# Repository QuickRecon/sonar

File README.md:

# Sonar

SonarMK2 is a standalone underwater sonar imaging system. An ESP32 drives a Blue Robotics Ping360 mechanical scanning sonar over RS-485, reads depth from a pressure sensor, and hosts a WiFi access point that serves a real-time polar sonar display to any browser that connects. The ESP hosts a webserver and "realtime" data is streamed over websockets, the page also uses the browser datastore to record the sonar information which can be downloaded and replayed using [text](Firmware/tools/replay.html). There is eventual intention to use the sonar for SLAM and some data analysis has occured in that direction, however this is ongoing.

## Hardware

The core is an ESP32-WROOM-32 with 2 MB flash and no PSRAM. The Ping360 communicates at 115200 baud over a half-duplex RS-485 link with automatic direction control on the DE pin. Depth comes from an MS5837-30BA pressure sensor on I2C at 400 kHz. Four status LEDs give a visual indicator of where the device is in its startup sequence.

Power input is from a battery connector (7–12 V) or USB-C, with an auto-select mux (TPS2121) handling the switch. A boost converter generates the 12 V rail for the sonar; a separate 5 V rail powers the RS-485 and external connectors. Both rails are software-controlled, so the firmware brings them up in sequence and checks power-good signals before proceeding.

The PCB also includes a CAN bus transceiver (TCAN334), the intended use is to allow for expansion to either DPV control/monitoring, or to be attached to a DiveCAN system so that rebreather information can be shown on the same display.

The hardware design files are in `EDA/` (KiCad schematic and PCB) and `CAD/` (FreeCAD housing assembly with STEP exports).

## Firmware

The firmware is built on ESP-IDF v6.0.0 and organized into nine components with no upward dependencies:

- **rs485** — UART1 half-duplex driver with automatic DE control
- **ping_protocol** — Binary frame encoder and decoder, pure C with no ESP-IDF coupling
- **ping360** — Scan task, configuration management, device probing
- **ms5837** — I2C pressure and depth sensor with full second-order compensation
- **led** — Four status LEDs indicating boot progress
- **power** — Rail enable/disable and battery voltage ADC
- **canbus** — CAN bus init and send (scaffolded, not called from main, will eventually have DiveCAN layer)
- **wifi_ap** — WiFi access point with captive portal DNS
- **web_server** — HTTPS file serving and WebSocket broadcast

### TLS Certificates

The web server uses HTTPS with a self-signed certificate. Generate the cert and key before building:

```bash
mkdir -p Firmware/certs
openssl req -x509 -newkey ec -pkeyopt ec_paramgen_curve:prime256v1 \
  -keyout Firmware/certs/server.key -out Firmware/certs/server.pem \
  -days 3650 -nodes -subj "/CN=sonar.local"
```

These files are gitignored — each device should have its own keypair.

The layering is intentional. `ping_protocol` can be compiled and tested on a host machine without any embedded toolchain. `ping360` depends on `rs485` and `ping_protocol` but knows nothing about networking. `web_server` reaches into `ping360` only for config get/set. This keeps the components independently testable and prevents the kind of circular dependency that becomes painful as a codebase grows.

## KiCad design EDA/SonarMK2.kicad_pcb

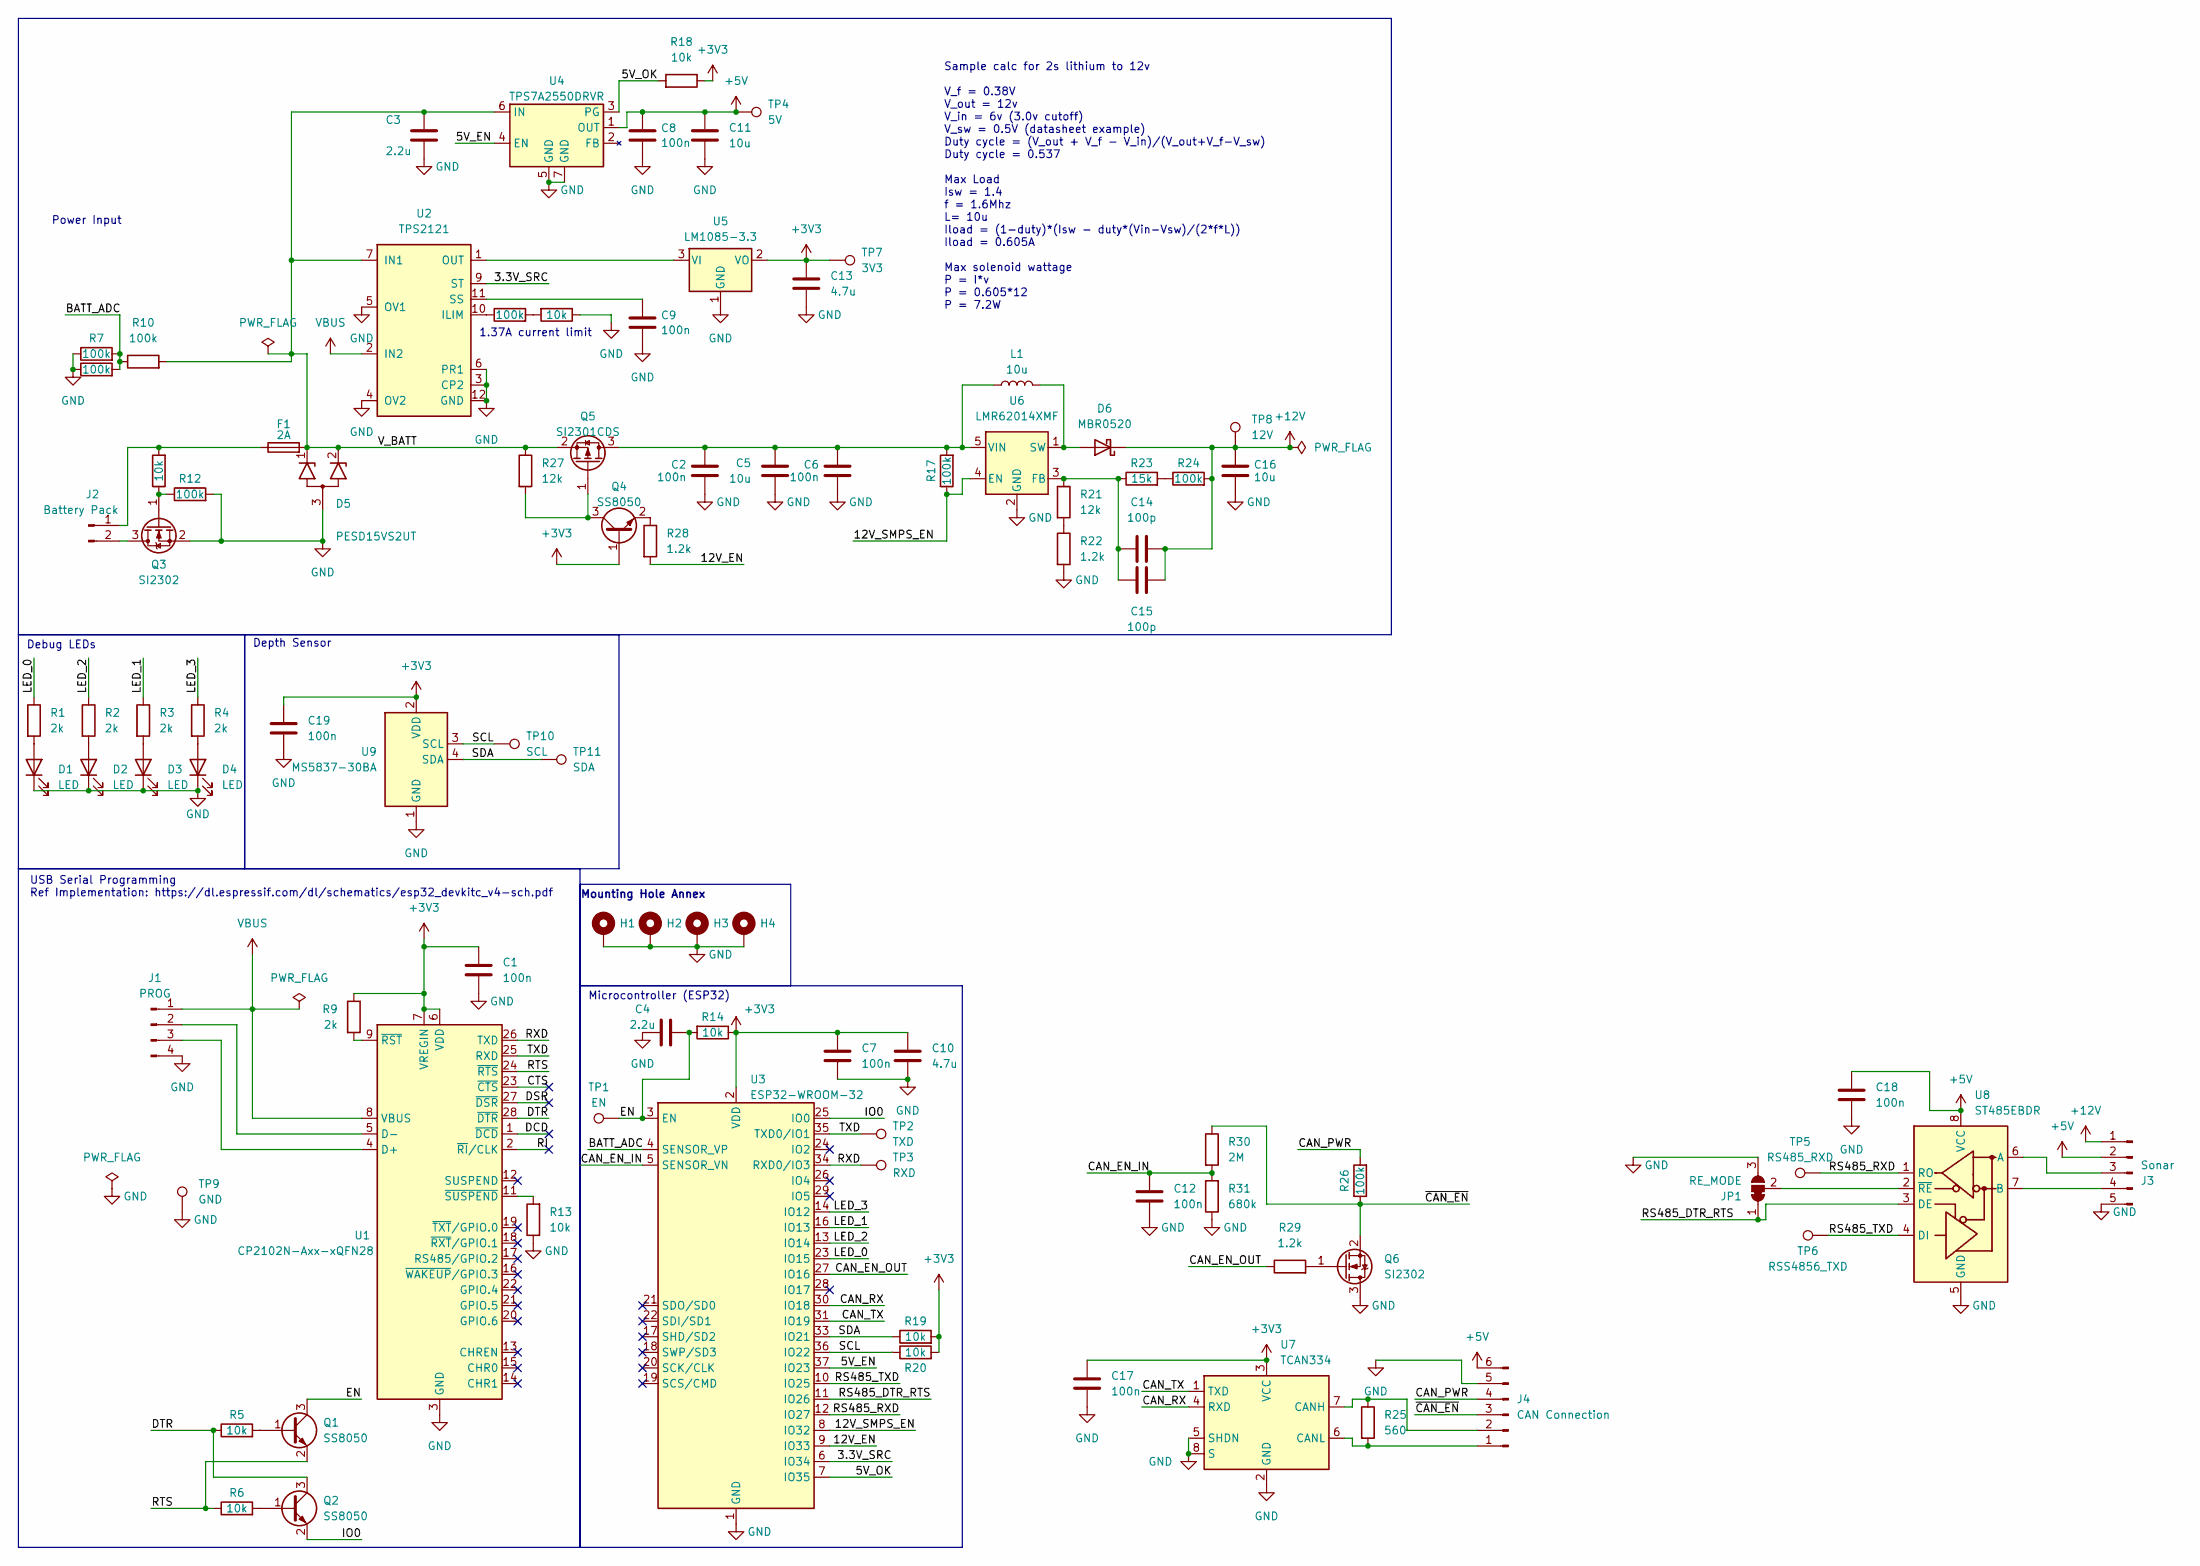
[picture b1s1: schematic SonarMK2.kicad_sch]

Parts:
C1, C7, C12: 100n; C_0402_1005Metric; MPN C1525
C2, C6, C8, C9, C17, C18, C19: 100n; C_0603_1608Metric; MPN C14663
C3, C4: 2.2u; C_0805_2012Metric; MPN C377773
C5, C11, C16: 10u; C_0603_1608Metric; MPN C96446
C10, C13: 4.7u; C_0805_2012Metric; MPN C1779
C14, C15: 100p; C_0402_1005Metric; MPN C1546
D1, D2, D3, D4: LED; LED_0805_2012Metric; MPN C84256
D5: PESD15VS2UT; SOT-23; MPN C2831524
D6: MBR0520; D_SOD-123; MPN C5204745
F1: 2A; Fuseholder_Littelfuse_Nano2_154x; MPN C108518
H1, H2, H3, H4: MountingHole_Pad; MountingHole_3.2mm_M3_Pad
J1: PROG; PinHeader_1x04_P2.54mm_Vertical
J2: Battery Pack; PinHeader_1x02_P2.54mm_Vertical
J3: Sonar; PinHeader_1x05_P2.54mm_Vertical
J4: CAN Connection; PinHeader_1x06_P2.54mm_Vertical
JP1: RE_MODE; SolderJumper-3_P1.3mm_Bridged2Bar12_RoundedPad1.0x1.5mm
L1: 10u; L_SunItech_SLO0530H; MPN C325966
Q1, Q2, Q4: SS8050; SOT-23; MPN C2150
Q3, Q6: SI2302; SOT-23; MPN C382300; JlcRotOffset 180
Q5: SI2301CDS; TSOT-23; MPN C10487
R1, R2, R3, R4, R9: 2k; R_0402_1005Metric; MPN C4109
R5, R6, R11, R13, R14, R16, R18, R19, R20: 10k; R_0402_1005Metric; MPN C25744
R7, R8, R10, R12, R15, R17, R24, R26: 100k; R_0402_1005Metric; MPN C25741
R21, R27: 12k; R_0402_1005Metric; MPN C25752
R22, R28, R29: 1.2k; R_0402_1005Metric; MPN C25862
R23: 15k; R_0402_1005Metric; MPN C25756
R25: 560; R_0805_2012Metric; MPN C28636
R30: 2M; R_0603_1608Metric; MPN C22976
R31: 680k; R_0603_1608Metric; MPN C25822
TP1: EN; TestPoint_THTPad_2.0x2.0mm_Drill1.0mm
TP2: TXD; TestPoint_THTPad_2.0x2.0mm_Drill1.0mm
TP3: RXD; TestPoint_THTPad_2.0x2.0mm_Drill1.0mm
TP4: 5V; TestPoint_THTPad_2.0x2.0mm_Drill1.0mm
TP5: RS485_RXD; TestPoint_THTPad_2.0x2.0mm_Drill1.0mm
TP6: RSS4856_TXD; TestPoint_THTPad_2.0x2.0mm_Drill1.0mm
TP7: 3V3; TestPoint_THTPad_2.0x2.0mm_Drill1.0mm
TP8: 12V; TestPoint_THTPad_2.0x2.0mm_Drill1.0mm
TP9: GND; TestPoint_THTPad_2.0x2.0mm_Drill1.0mm
TP10: SCL; TestPoint_THTPad_2.0x2.0mm_Drill1.0mm
TP11: SDA; TestPoint_THTPad_2.0x2.0mm_Drill1.0mm
U1: CP2102N-Axx-xQFN28; QFN-28-1EP_5x5mm_P0.5mm_EP3.35x3.35mm; MPN C6568
U2: TPS2121; Texas_VQFN-HR-12_2x2.5mm_P0.5mm; JLC Part # C485916
U3: ESP32-WROOM-32; MPN C701342
U4: TPS7A2550DRVR; WSON-6-1EP_2x2mm_P0.65mm_EP1x1.6mm_ThermalVias; MPN C2876265; JlcRotOffset 0
U5: LM1085-3.3; TO-263-3_TabPin2; MPN C444380
U6: LMR62014XMF; SOT-23-5; MPN C468235
U7: TCAN334; SOIC-8_3.9x4.9mm_P1.27mm; MPN C2871143; JlcRotOffset -90
U8: ST485EBDR; SOIC-8_3.9x4.9mm_P1.27mm; MPN C81186
U9: MS5837-30BA; TE_MS5837-xxBA; MPN C2887941

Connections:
+3V3: C1.1, C7.1, C10.1, C13.1, C17.1, C19.1, Q4.1 (B), R9.1, R14.1, R18.1, R19.2, R20.2, TP7.1, U1.6 (VDD), U1.7 (VREGIN), U3.2 (VDD), U5.2 (VO), U7.3 (VCC), U9.2 (VDD)
+5V: C8.1, C11.1, C18.1, J3.2, J4.6, TP4.1, U4.1 (OUT), U8.8 (VCC)
+12V: C14.1, C15.1, C16.1, D6.1 (K), J3.1, R24.2, TP8.1
/3.3V_SRC: U2.9 (ST), U3.6 (IO34)
/5V_EN: U3.37 (IO23), U4.4 (EN)
/5V_OK: R18.2, U3.7 (IO35), U4.3 (PG)
/12V_EN: R28.2, U3.9 (IO33)
/12V_SMPS_EN: R17.1, U3.8 (IO32), U6.4 (EN)
/BATT_ADC: R7.2, R8.2, R10.1, U3.4 (SENSOR_VP)
/CAN_EN_IN: C12.1, R30.2, R31.2, U3.5 (SENSOR_VN)
/CAN_EN_OUT: R29.1, U3.27 (IO16)
/CAN_PWR: J4.4, R26.2
/CAN_RX: U3.30 (IO18), U7.4 (RXD)
/CAN_TX: U3.31 (IO19), U7.1 (TXD)
/CTS: U1.23 (~CTS)
/DCD: U1.1 (~DCD)
/DSR: U1.27 (~DSR)
/DTR: Q2.3 (C), R5.1, U1.28 (~DTR)
/EN: C4.2, Q1.3 (C), R14.2, TP1.1, U3.3 (EN)
/IO0: Q2.2 (E), U3.25 (IO0)
/LED_0: R1.1, U3.23 (IO15)
/LED_1: R3.1, U3.16 (IO13)
/LED_2: R2.1, U3.13 (IO14)
/LED_3: R4.1, U3.14 (IO12)
/RI: U1.2 (~RI/CLK)
/RS485_DTR_RTS: JP1.1 (A), U3.11 (IO26), U8.3 (DE)
/RS485_RXD: TP5.1, U3.12 (IO27), U8.1 (RO)
/RS485_TXD: TP6.1, U3.10 (IO25), U8.4 (DI)
/RTS: Q1.2 (E), R6.1, U1.24 (~RTS)
/RXD: TP3.1, U1.26 (TXD), U3.34 (RXD0/IO3)
/SCL: R20.1, TP10.1, U3.36 (IO22), U9.3 (SCL)
/SDA: R19.1, TP11.1, U3.33 (IO21), U9.4 (SDA)
/TXD: TP2.1, U1.25 (RXD), U3.35 (TXD0/IO1)
/V_BATT: C3.1, D5.1 (K1), D5.2 (K2), F1.2, Q5.2 (S), R10.2, R27.1, U2.7 (IN1), U4.6 (IN)
/~CAN_EN: J4.3, Q6.2 (S), R26.1, R30.1
GND: C1.2, C2.1, C3.2, C4.1, C5.2, C6.1, C7.2, C8.2, C9.2, C10.2, C11.2, C12.2, C13.2, C16.2, C17.2, C18.2, C19.2, D1.1 (K), D2.1 (K), D3.1 (K), D4.1 (K), D5.3 (A), H1.1, H2.1, H3.1, H4.1, J1.4, J3.5, J4.5, JP1.3 (B), Q3.2 (S), Q6.3 (D), R7.1, R8.1, R12.2, R13.1, R16.1, R22.2, R31.1, TP9.1, U1.3 (GND), U1.29 (GND), U2.3 (CP2), U2.4 (OV2), U2.5 (OV1), U2.6 (PR1), U2.12 (GND), U3.1 (GND), U3.15 (GND), U3.38 (GND), U3.39 (GND), U4.5 (GND), U4.7 (GND), U5.1 (GND), U6.2 (GND), U7.2 (GND), U7.5 (SHDN), U7.8 (S), U8.5 (GND), U9.1 (GND)
unnamed: D1.2 (A), R1.2
unnamed: D2.2 (A), R2.2
unnamed: D3.2 (A), R3.2
unnamed: D4.2 (A), R4.2
unnamed: D6.2 (A), L1.2, U6.1 (SW)
unnamed: J1.2, U1.5 (D-)
unnamed: J1.3, U1.4 (D+)
unnamed: F1.1, J2.1, R11.2
unnamed: J2.2, Q3.3 (D)
unnamed: J3.3, U8.6 (A)
unnamed: J3.4, U8.7 (B)
unnamed: J4.1, R25.2, U7.6 (CANL)
unnamed: J4.2, R25.1, U7.7 (CANH)
unnamed: JP1.2 (C), U8.2 (~RE)
unnamed: Q1.1 (B), R5.2
unnamed: Q2.1 (B), R6.2
unnamed: Q3.1 (G), R11.1, R12.1
unnamed: Q4.3 (C), Q5.1 (G), R27.2
unnamed: Q4.2 (E), R28.1
unnamed: C2.2, C5.1, C6.2, L1.1, Q5.3 (D), R17.2, U6.5 (VIN)
unnamed: Q6.1 (G), R29.2
unnamed: R15.2, R16.2
unnamed: R21.2, R22.1
unnamed: R23.2, R24.1
unnamed: R9.2, U1.9 (~RST)
unnamed: R13.2, U1.11 (~SUSPEND)
unnamed: R15.1, U2.10 (ILIM)
unnamed: C9.1, U2.11 (SS)
unnamed: U2.1 (OUT), U2.8 (OUT), U5.3 (VI)
unnamed: C14.2, C15.2, R21.1, R23.1, U6.3 (FB)
VBUS: J1.1, U1.8 (VBUS), U2.2 (IN2)

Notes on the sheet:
Power Input
1.37A current limit
Depth Sensor
USB Serial Programming Ref Implementation: https://dl.espressif.com/dl/schematics/esp32_devkitc_v4-sch.pdf
Sample calc for 2s lithium to 12v V_f = 0.38V V_out = 12v V_in = 6v (3.0v cutoff) V_sw = 0.5V (datasheet example) Duty cycle = (V_out + V_f - V_in)/(V_out+V_f-V_sw) Duty cycle = 0.537 Max Load Isw = 1.4 f = 1.6Mhz L= 10u Iload = (1-duty)*(Isw - duty*(Vin-Vsw)/(2*f*L)) Iload = 0.605A Max solenoid wa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
Debug LEDs
Microcontroller (ESP32)
Mounting Hole Annex

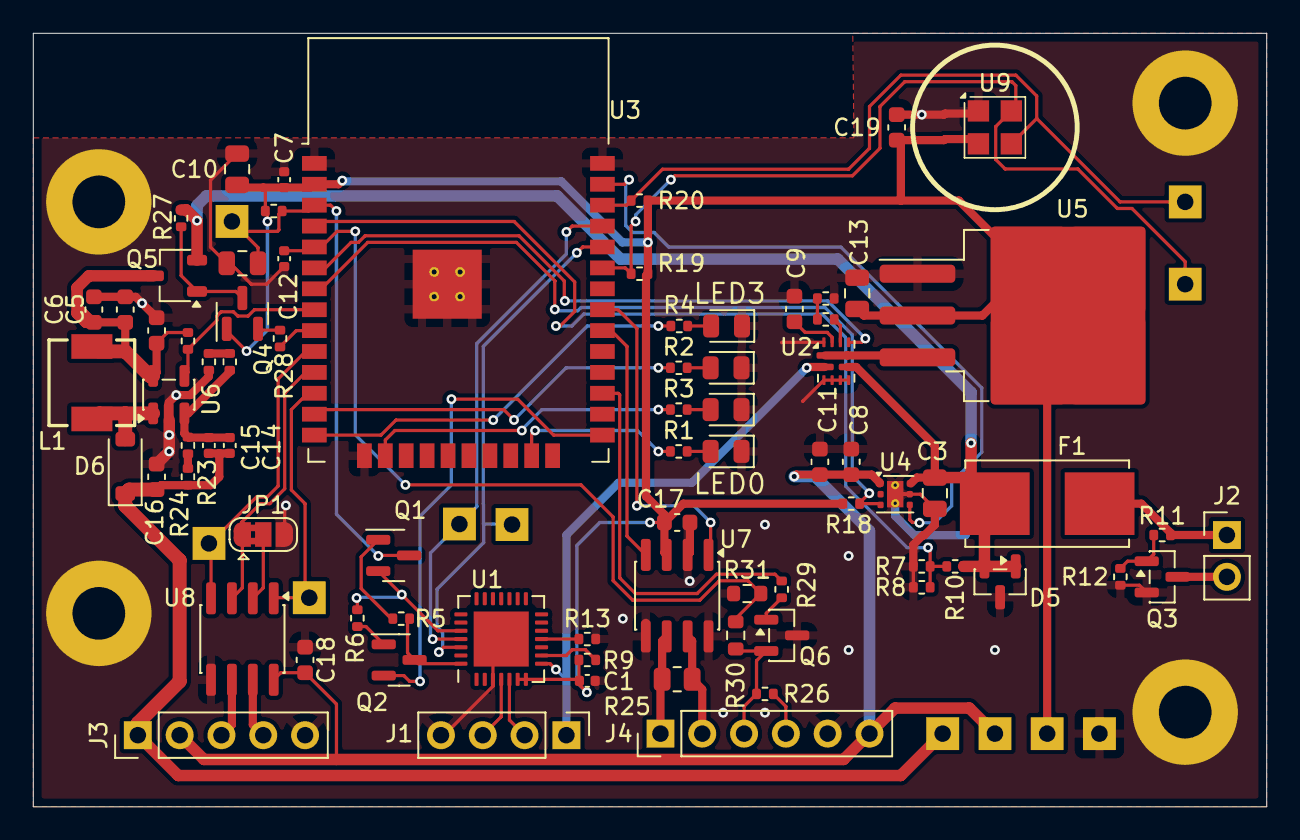
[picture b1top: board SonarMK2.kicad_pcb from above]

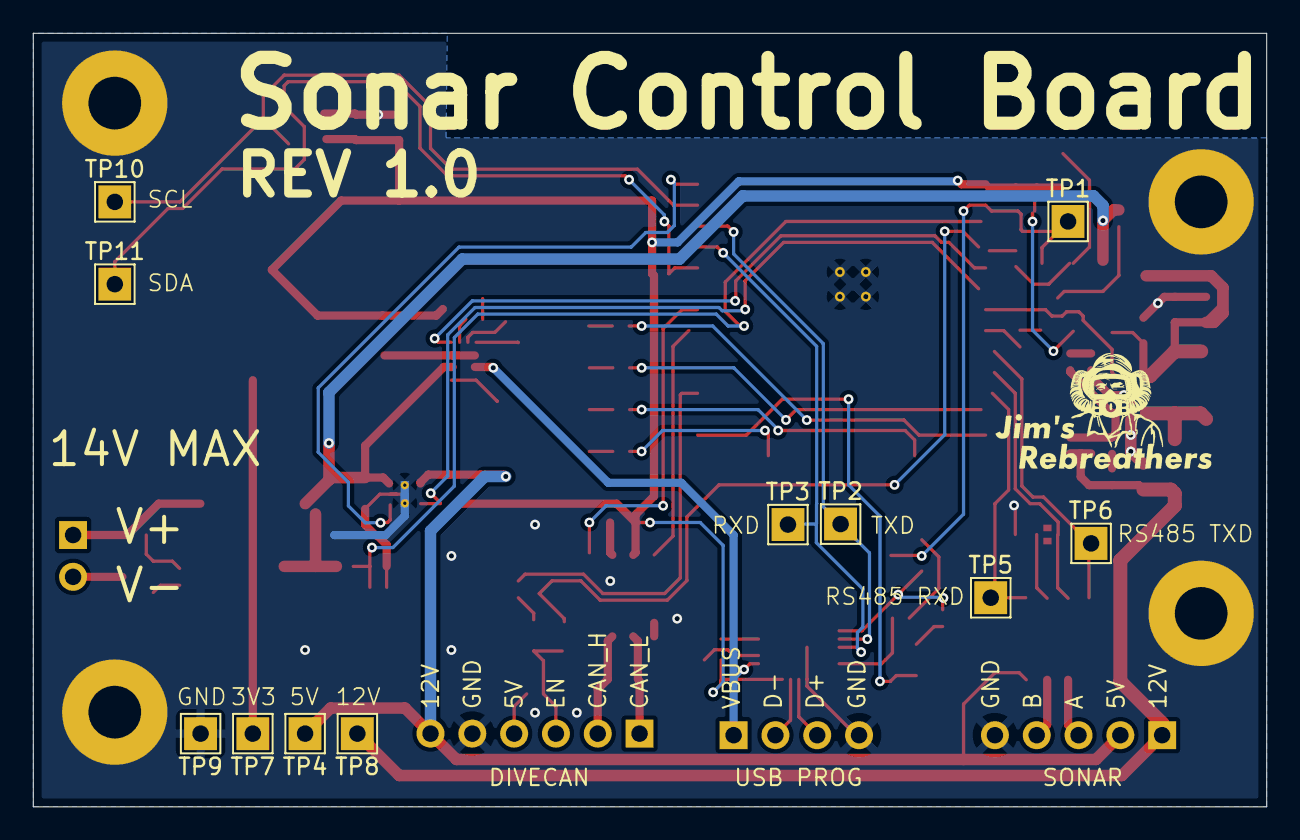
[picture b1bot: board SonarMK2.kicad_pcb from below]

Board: 2 copper layers, 74.9 x 47.0 mm, 93 parts (11 on the bottom side), 63 nets.

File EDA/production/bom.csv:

Designator,Footprint,Quantity,Value,LCSC Part #
"C1, C12, C7",0402,3,100n,C1525
"C10, C13",0805,2,4.7u,C1779
"C11, C16, C5",0603,3,10u,C96446
"C14, C15",0402,2,100p,C1546
"C17, C18, C19, C2, C6, C8, C9",0603,7,100n,C14663
"C3, C4",0805,2,2.2u,C377773
"D1, D2, D3, D4",0805,4,LED,C84256
D5,SOT-23,1,PESD15VS2UT,C2831524
D6,D_SOD-123,1,MBR0520,C5204745
F1,Fuseholder_Littelfuse_Nano2_154x,1,2A,C108518
JP1,SolderJumper-3_P1.3mm_Bridged2Bar12_RoundedPad1.0x1.5mm,1,RE_MODE,
L1,L_SunItech_SLO0530H,1,10u,   C325966
"Q1, Q2, Q4",SOT-23,3,SS8050,C2150
"Q3, Q6",SOT-23,2,SI2302,C382300
Q5,TSOT-23,1,SI2301CDS,C10487
"R1, R2, R3, R4, R9",0402,5,2k,C4109
"R10, R12, R15, R17, R24, R26, R7, R8",0402,8,100k,C25741
"R11, R13, R14, R16, R18, R19, R20, R5, R6",0402,9,10k,C25744
"R21, R27",0402,2,12k,C25752
"R22, R28, R29",0402,3,1.2k,C25862
R23,0402,1,15k,C25756
R25,0805,1,560,C28636
R30,0603,1,2M,C22976
R31,0603,1,680k,C25822
U1,QFN-28-1EP_5x5mm_P0.5mm_EP3.35x3.35mm,1,CP2102N-Axx-xQFN28,C6568
U2,Texas_VQFN-HR-12_2x2.5mm_P0.5mm,1,TPS2121,
U3,ESP32-WROOM-32,1,ESP32-WROOM-32,C701342
U4,WSON-6-1EP_2x2mm_P0.65mm_EP1x1.6mm_ThermalVias,1,TPS7A2550DRVR,C2876265
U5,TO-263-3_TabPin2,1,LM1085-3.3,C444380
U6,SOT-23-5,1,LMR62014XMF,C468235
U7,SOIC-8_3.9x4.9mm_P1.27mm,1,TCAN334,C2871143
U8,SOIC-8_3.9x4.9mm_P1.27mm,1,ST485EBDR,C81186
U9,TE_MS5837-xxBA,1,MS5837-30BA,C2887941

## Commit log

2026-02-11 init
2026-02-11 Initial clauding
2026-02-13 Dump some AI friendly docs
2026-02-13 Get web working
2026-02-13 Get rid of spiffs to better support ota later
2026-02-13 Web fixing
2026-02-13 Calculate parameters on-esp
2026-02-13 Improve test pattern
2026-02-13 Add turbo color pattern
2026-02-13 Add sonar datastore
2026-02-13 Get talking to the ping
2026-02-13 Enable snapping to angles
2026-02-13 UX improvements
2026-02-13 Add a menu toggle
2026-02-14 Add scan mode
2026-02-14 Improve power sequencing
2026-02-14 Add some robustification to the sockets
2026-02-14 Add some diagnostics
2026-02-14 Fix mem issue in web server
2026-02-14 Change 500 samples to 600 samples to avoid sonar firmware issue
2026-02-15 Autoscale canvas
2026-02-15 UI changes from pool test
2026-02-15 Compass tracking
2026-02-15 change to a more robust dns implementation
2026-02-16 Add depth zero button
2026-02-17 store config
2026-02-17 Compass LPF
2026-02-18 Add recording
2026-02-18 Make the text more legible
2026-02-19 Fix depth sensor overreading
2026-02-21 Make some enhancements to the replay tool
2026-02-22 more slam analytics
2026-02-23 Add continuous slider
2026-03-05 Add CAD, EDA, and project docs to version control
    Move git root from Firmware/ to SonarMK2/ and bring CAD (FreeCAD) and
    EDA (KiCAD) design files under version control alongside firmware.
2026-03-05 Add readme, remove AI junk
2026-03-05 Update gitignore and readme with certs directory
2026-03-05 Move readme to toplevel dir
2026-03-05 Add license
2026-03-05 Add images to readme
